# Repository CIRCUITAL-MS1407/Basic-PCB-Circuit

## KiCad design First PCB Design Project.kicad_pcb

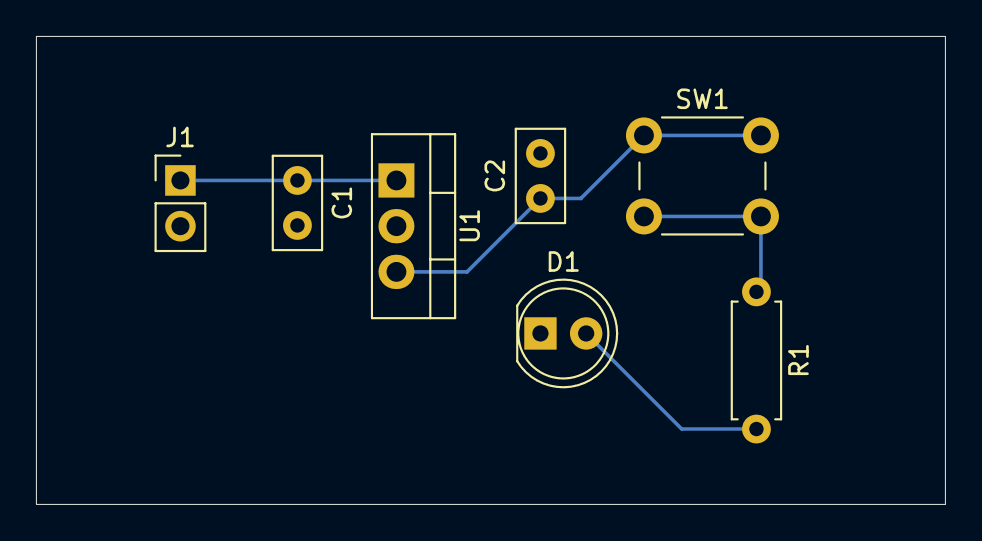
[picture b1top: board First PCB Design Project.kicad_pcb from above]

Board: 2 copper layers, 50.5 x 26.0 mm, 7 parts (0 on the bottom side), 5 nets.

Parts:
C1: 0.22uf; C_Disc_D5.0mm_W2.5mm_P2.50mm
C2: 0.1uf; C_Disc_D5.0mm_W2.5mm_P2.50mm
D1: LED; LED_D5.0mm_Clear
J1: Conn_01x02_Pin; PinHeader_1x02_P2.54mm_Vertical
R1: R; R_Axial_DIN0207_L6.3mm_D2.5mm_P7.62mm_Horizontal
SW1: SW_Push; SW_PUSH_6mm_H5mm
U1: L7805; TO-220-3_Vertical

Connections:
GND: C1.2, C2.2, D1.1 (K), J1.2, U1.2 (GND)
unnamed: D1.2 (A), R1.2
unnamed: C1.1, J1.1, U1.1 (IN)
unnamed: R1.1, SW1.2
unnamed: C2.1, SW1.1, U1.3 (OUT)
